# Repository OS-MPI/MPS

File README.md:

# The Magnetic Particle Spectroscopy (MPS) device
# [Link to the wiki](https://github.com/OS-MPI/MPS/wiki)
# [Link to the Main OS-MPI Page](https://os-mpi.github.io/)

## Motivation and Introduction

The system we are calling the MPS device is a low cost, and fairly simple to manufacture project which more generally speaking is a platform designed around understanding magnetic characteristics of superparamagentic iron oxide nanoparticles (SPIONs). The motivation was to condense the numerous existing systems into a singlular platform capable of providing insights into the nanoparticles irrespective of the specific goal of the lab. With that in mind, calling our platform an "MPS" system is rather imprecise; while one mode is traditional "spectroscopy" the device is designed to be flexible and able to perform relaxometry measurements as well as magnetometry, yet in order to give the project an easy-to-find, descriptive name, we settled on the "magnetic particle spectroscopy" system. 

## State of the project

In the current state (of March 2024) we have the system working in all [primary operational modes](https://github.com/OS-MPI/MPS/wiki/Modes-of-operation). It is capable of sensitively detecting SPIONs to the ng Fe level, quantifying the magnetization spectra, tracing the hysteresis loops, etc. 

The primary focus now is improving the documentation.

## System overview

Broadly speaking, there are four principle hardware components, the three coils (drive, receive, and bias) and the sample positioner. The drive coils produce magnetic fields (typ. 10 mT) which cause the SPIONs within the bore to go into and out of saturation at 23.8 kHz. This changing magnetism induces a voltage in the receive coils. The bias coils allow for the quasistatic operating point of the SPIONs to be modulated by generating low frequency (~10 Hz) fields up to about 50 mT.

### Drive/Transmit system
The drive system consists of the drive coils as well as the amplifier and filter. 

The drive coil is seen in the photograph above (the larger coil with four sub-sections). All of the four winding sections are in the same handedness. See the Wiki for further details. 

In this photograph, we utilize an in-house made Litz wire (18 strands of 28 AWG magnet wire), although other Litz wires may work similarly well. Previously a commercial Litz wire with 115 strands of 36AWG was used, but because of the plastic sleeve over the wires, they could not be easily stabilized with epoxy. 

The drive filter serves to purify and the waveform produced by the amplifier. Most amplifiers produce about 0.1% (or worse) total harmonic distortion, so without this filter those amplifier-generated distortions will dominate the noise floor. That being said, its among the most challenging components to manufacture, so its worth discussing which components are essential, and which are more or less optional. Refering to the schematic below, the two most important sections are the tuning/matching capacitors (C1 and C2), and the transformer (LPri and LSec). The tuning capacitors form a resonant circuit with Ldrive (the drive coil's equivalent load). This can be seen if you notice the loop formed by C1 C2 and LDrive is resonant. The choice of values for C1 and C2 is to make the equivalent impedance 8 ohms or so. The transformer should be a ferrite such as N87 and be designed such that the core flux is well below saturation (~20x lower, so 20ish mT). The purpose is to mitigate common-mode noise and provide isolation/break any ground loops. The other filter components can be "dropped in" later without disturbing the overall circuit. But these additional filtering components are both the most challenging to build, and less necessary. 

Many different drive amplifiers can be used. We have used both linear and switch-mode amplifiers with success. For a basic system, the AIYIMA A07 can be used, or other amplifiers based on the TPA3255 will likely be good choices. For example Nobsound G2 pro is also likely good and is pre-configured to be in PBTL mode. That IC from Texas Instruments has excellent performance given the cost and high switching frequency. The AE Techron 7224 is considerably more expensive, but produces a much higher fidelity waveform and has far more power available.

### Receive system

The receive system consists of the gradiometer receive coils, the filter, matching transformer, and preamplifier. The receive coil is a simple gradiometer to mitigate the net voltage induced from the changing magnetic drive fields (60-80 dBc attenuation of the voltage is a reasonable target). The filter reduces the amplitude of the signal at the drive frequency, but doesnt fully remove it. The matching transformer steps up the voltage produced by the receive coil (post filter) to improve the noise performance of the system. The transformer also provides isolation and common-mode supression, which help signal fidelity. The preamplifier amplifies the signal to a level more usable by the data acquisition hardware. In our case, we digitize the signals with a National Instruments NI PXIe 6363 and 6361. 

### Bias system

The bias system applies a low frequency (~10Hz), high amplitude waveform to probe the magnetization response at different quasistatic operating points. "Quasistatic" is emphasized here just because we utilize the assumption that this frequency is so low relaxation effects are negligible.

The system was initially designed to allow for even very small SPIONs (e.g. 5nm) to be probed out toward saturation, so many turns were added and cooling spaces were added to allow air to pass between the windings. With this design, passive convection is sufficient for normal operation at 50 mT peak. For up to 100 mT peak, lower duty cycles, or forced air should be used. 

This coil can be neglected if only hysteresis loop tracing or spectroscopy modes will be used. In that case, the diameter of the shielding tube should be increased to about 50-60 mm diameter. 

### Sample positioner

An automatic sample positioner is used to allow for consistent placement of the SPIONs as well as having the sample move in and out repeatedly to allow for multiple baselines to acquired. 

### Software

The software is written with LabVIEW 2021. Labview is not backwards compatible, so it must be operated with version 2021 or newer. 

With any issues regarding the project or missing files/documentation, [please reach out to the authors of this project here](https://github.com/OS-MPI/MPS/wiki/Contact-Us).

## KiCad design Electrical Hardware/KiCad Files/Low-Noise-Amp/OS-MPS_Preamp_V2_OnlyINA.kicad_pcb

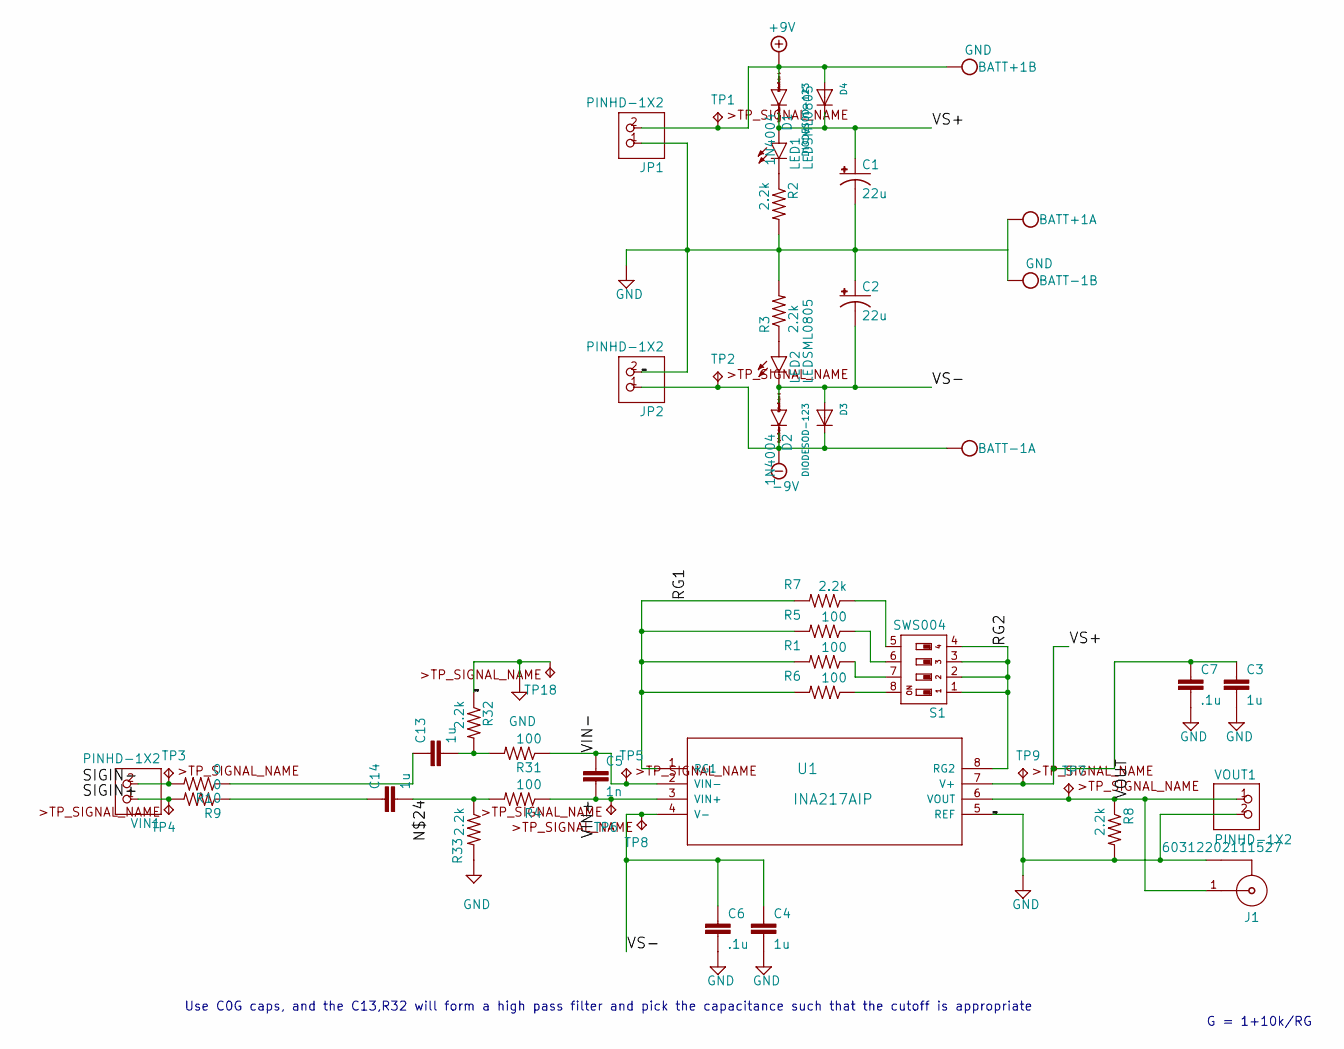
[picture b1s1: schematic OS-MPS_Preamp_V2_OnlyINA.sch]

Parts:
BATT+1: GND; W237-102
BATT-1: GND; W237-102
C1, C2: 22u; TT2D6
C3, C4, C13, C14: 1u; C1206
C5: 1n; C1206
C6, C7: .1u; C1206
D1, D2: 1N4004; DO41-10
D3, D4: DIODESOD-123; SOD-123
J1: 60312202111527
JP1, JP2: PINHD-1X2; 1X02
LED1, LED2: LEDSML0805; SML0805
R1, R4, R5, R6, R31: 100; R0805
R2, R3, R7, R8, R32, R33: 2.2k; R0805
R9, R10: 0; R0805
S1: SWS004; SMS-004
TP1, TP2: TPB2,54; B2,54
TP3, TP4, TP5, TP6, TP7, TP8, TP9, TP18: TPTP20SQ; TP20SQ
U1: INA217AIP; P8
VIN1: PINHD-1X2; 1X02
VOUT1: PINHD-1X2; 1X02

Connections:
+9V: BATT+1.2, D1.A, D4.A, JP1.2, TP1.TP
-9V: BATT-1.1, D2.C, D3.C, JP2.1, TP2.TP
/N$24: C14.2, R4.2, R33.1
/RG1: R1.2, R5.2, R6.2, R7.2, U1.1 (RG1)
/RG2: S1.1, S1.2, S1.3, S1.4, U1.8 (RG2)
/SIGIN+: R9.2, TP4.TP, VIN1.1
/SIGIN-: R10.2, TP3.TP, VIN1.2
/VIN+: C5.2, R4.1, TP6.TP, U1.3 (VIN+)
/VIN-: C5.1, R31.1, TP5.TP, U1.2 (VIN-)
/VOUT: J1.1, R8.1, TP7.TP, U1.6 (VOUT), VOUT1.1
/VS+: C1.+, C3.1, C7.1, D1.C, D4.C, LED1.A, TP9.TP, U1.7 (V+)
/VS-: C2.-, C4.1, C6.1, D2.A, D3.A, LED2.C, TP8.TP, U1.4 (V-)
GND: BATT+1.1, BATT-1.2, C1.-, C2.+, C3.2, C4.2, C6.2, C7.2, J1.2, J1.3 (2), J1.4 (2), J1.5 (2), JP1.1, JP2.2, R2.2, R3.2, R8.2, R32.1, R33.2, TP18.TP, U1.5 (REF), VOUT1.2
unnamed: C13.1, R10.1
unnamed: C13.2, R31.2, R32.2
unnamed: C14.1, R9.1
unnamed: LED1.C, R2.1
unnamed: LED2.A, R3.1
unnamed: R1.1, S1.7
unnamed: R5.1, S1.6
unnamed: R6.1, S1.8
unnamed: R7.1, S1.5

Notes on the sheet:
Use C0G caps, and the C13,R32 will form a high pass filter and pick the capacitance such that the cutoff is appropriate
G = 1+10k/RG

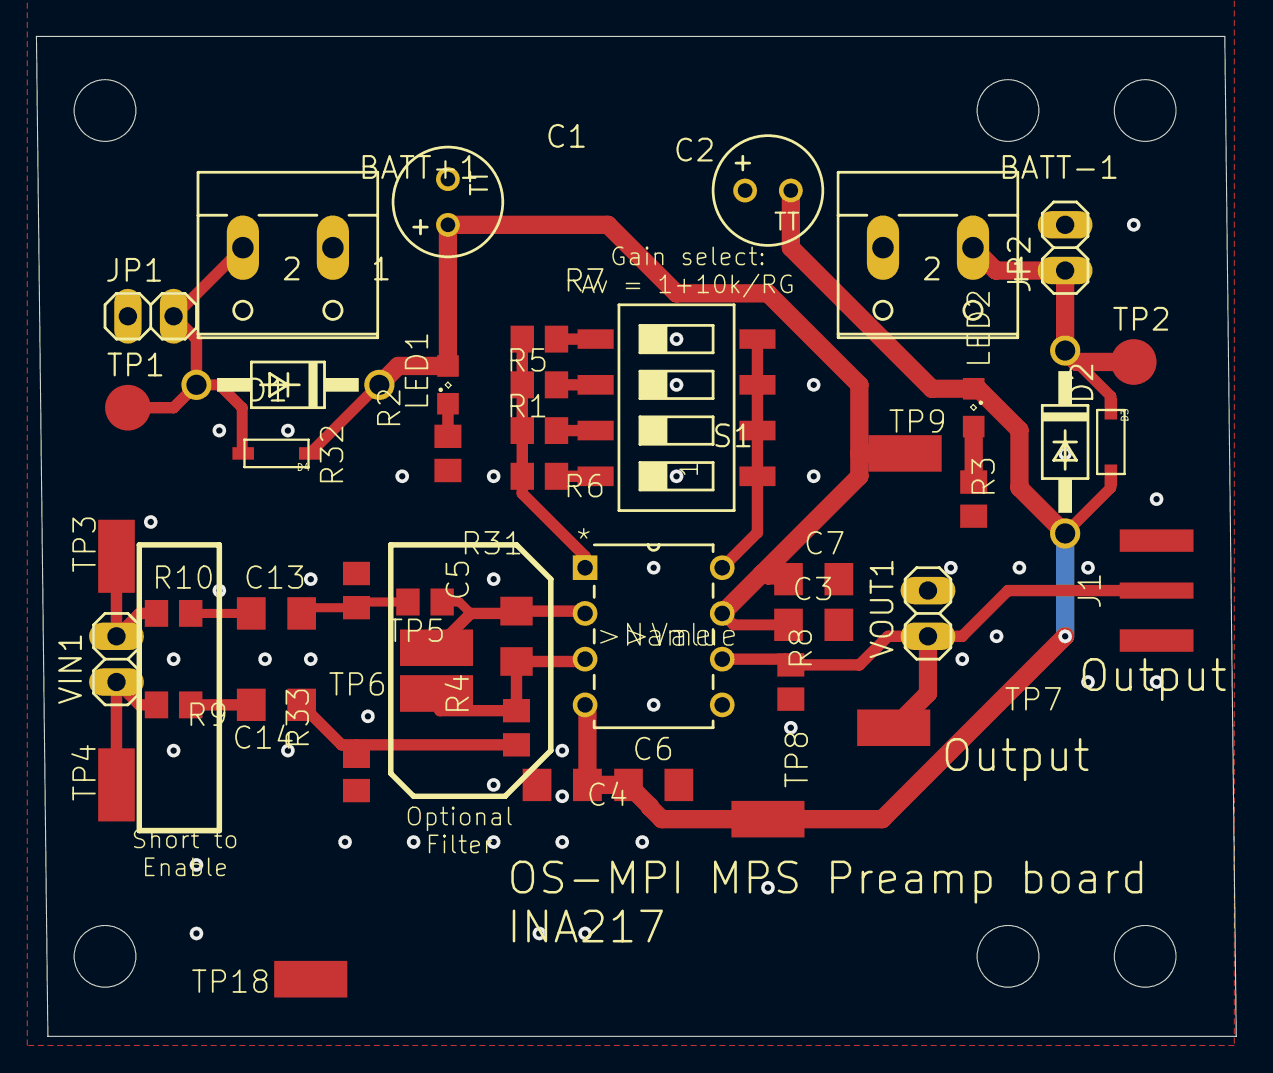
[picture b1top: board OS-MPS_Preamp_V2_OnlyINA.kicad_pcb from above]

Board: 2 copper layers, 66.7 x 55.6 mm, 53 parts (0 on the bottom side), 22 nets.

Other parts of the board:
@HOLE0, @HOLE1, @HOLE2, @HOLE3, @HOLE4, @HOLE5: (no value)

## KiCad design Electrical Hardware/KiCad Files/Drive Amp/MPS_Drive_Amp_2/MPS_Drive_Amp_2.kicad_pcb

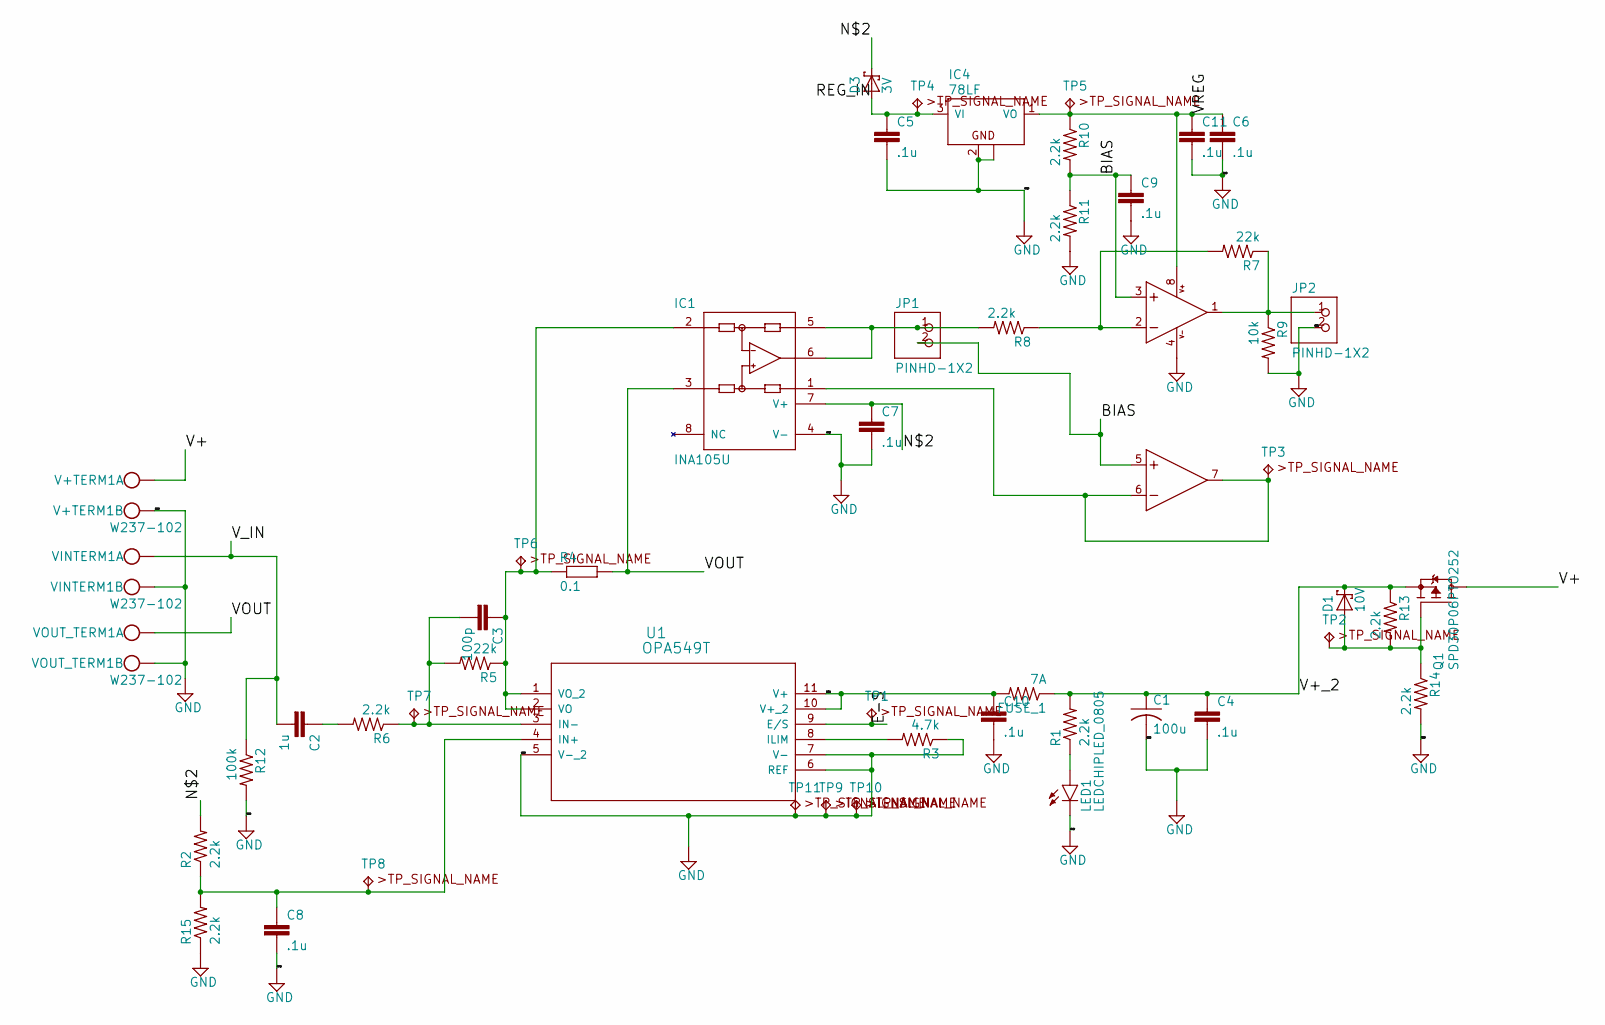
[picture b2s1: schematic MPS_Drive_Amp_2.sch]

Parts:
C1: 100u; C050-025X075
C2: 1u; C1206
C3: 100p; C1206
C4, C5, C6, C7, C8, C9, C10, C11: .1u; C1206
D1: 10V; DO35-7
D3: 3V; DO35-7
FUSE_1: 7A; R1206
IC1: INA105U; SO08
IC2: LM358MX; SO08
IC4: 78LF; SOT89
JP1, JP2: PINHD-1X2; 1X02
LED1: LEDCHIPLED_0805; CHIPLED_0805
Q1: SPD30P06PTO252; TO252
R1, R2, R6, R8, R10, R11, R13, R14, R15: 2.2k; R1206
R3: 4.7k; R1206
R4: 0.1; VTA52
R5, R7: 22k; R1206
R9: 10k; R1206
R12: 100k; R1206
TP1, TP2, TP3, TP4, TP5, TP6, TP7, TP8, TP9, TP10, TP11: TPTP20SQ; TP20SQ
U1: OPA549T; KV11
V+TERM1: W237-102
VINTERM1: W237-102
VOUT_TERM1: W237-102

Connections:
/BIAS: C9.1, IC2.3 (+IN), IC2.5 (+IN), JP1.2, R10.2, R11.1
/E-S: TP1.TP, U1.9 (E/S)
/N$2: C7.1, C10.1, D3.C, FUSE_1.2, IC1.7 (V+), R2.2, U1.10 (V+_2), U1.11 (V+)
/REG_IN: C5.1, D3.A, IC4.3 (VI), TP4.TP
/V+: Q1.3 (D), V+TERM1.1
/V+_2: C1.1, C4.1, D1.C, FUSE_1.1, Q1.2 (S), R1.2, R13.1
/VOUT: IC1.3 (+IN), R4.2, VOUT_TERM1.1
/VREG: C6.1, C11.1, IC2.8 (V+), IC4.1 (VO), R10.1, TP5.TP
/V_IN: C2.2, R12.1, VINTERM1.1
GND: C1.2, C4.2, C5.2, C6.2, C7.2, C8.2, C9.2, C10.2, C11.2, IC1.4 (V-), IC2.4 (V-), IC4.2 (GND), IC4.2@1 (GND@1), JP2.2, LED1.C, R3.1, R9.2, R11.2, R12.2, R14.2, R15.1, TP9.TP, TP10.TP, TP11.TP, U1.5 (V-_2), U1.6 (REF), U1.7 (V-), V+TERM1.2, VINTERM1.2, VOUT_TERM1.2
unnamed: C2.1, R6.2
unnamed: C3.1, IC1.2 (-IN), R4.1, R5.1, TP6.TP, U1.1 (VO_2), U1.2 (VO)
unnamed: C3.2, R5.2, R6.1, TP7.TP, U1.3 (IN-)
unnamed: C8.1, R2.1, R15.2, TP8.TP, U1.4 (IN+)
unnamed: D1.A, Q1.1 (G), R13.2, R14.1, TP2.TP
unnamed: IC1.1 (REF), IC2.6 (-IN), IC2.7 (OUT), TP3.TP
unnamed: IC1.5 (SENSE), IC1.6 (OUT), JP1.1, R8.2
unnamed: IC2.1 (OUT), JP2.1, R7.1, R9.1
unnamed: IC2.2 (-IN), R7.2, R8.1
unnamed: LED1.A, R1.1
unnamed: R3.2, U1.8 (ILIM)

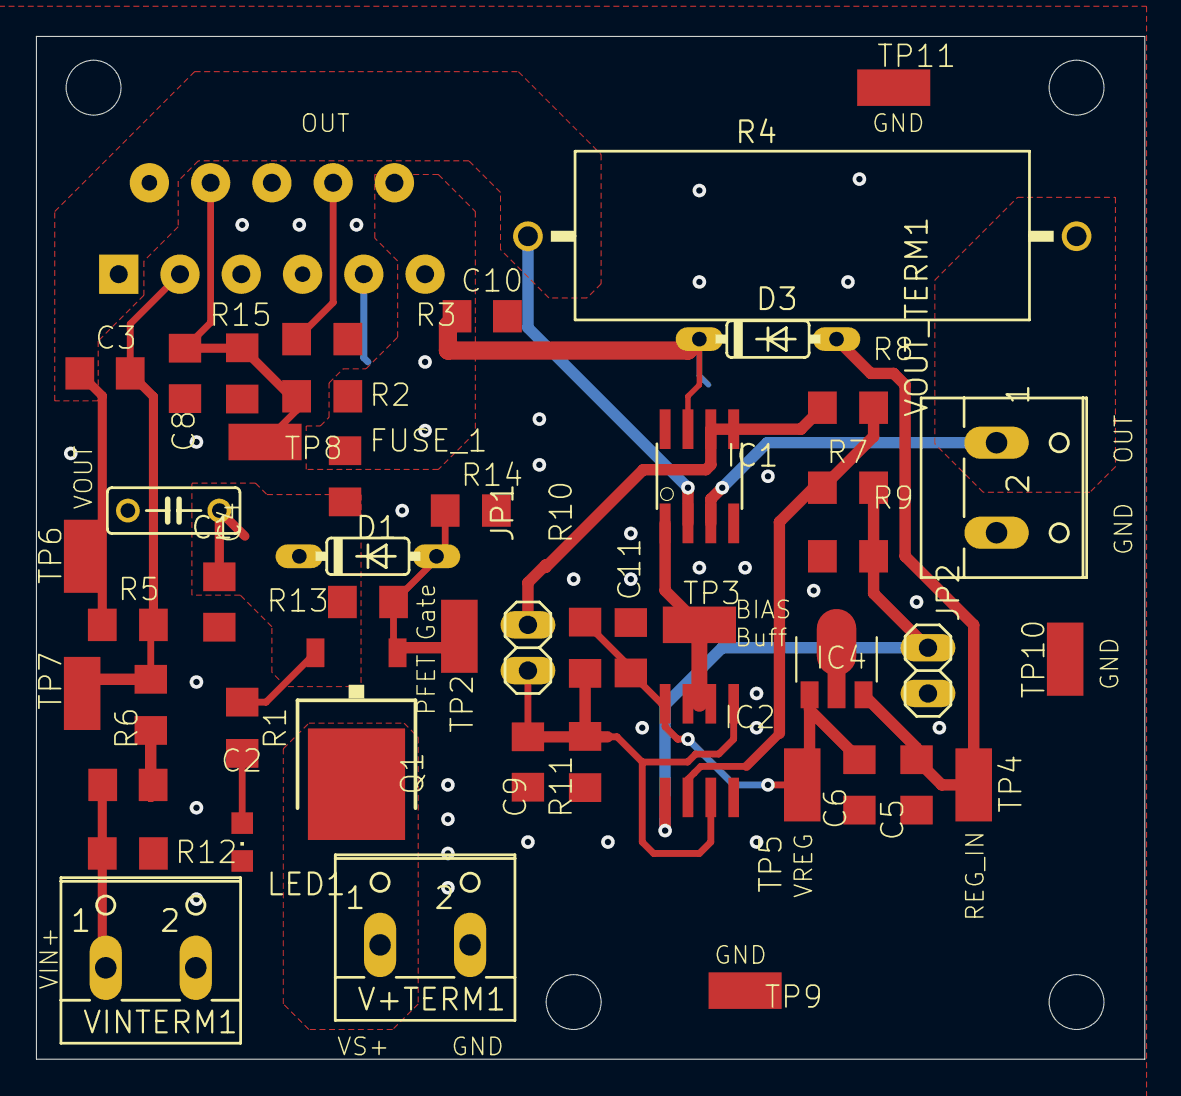
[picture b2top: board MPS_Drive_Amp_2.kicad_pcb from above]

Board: 2 copper layers, 61.6 x 56.8 mm, 55 parts (0 on the bottom side), 21 nets.

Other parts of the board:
@HOLE0, @HOLE1, @HOLE2, @HOLE3: (no value)

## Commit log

2019-12-01 Updatet_Part sheet
2019-12-02 Add Design Scripts
2020-02-17 Initial Inventor Part Push
2020-02-17 First MATLAB Script Push
2020-02-17 MATLAB Some Comments
    More commenting and cleaning code to come!
2020-02-17 Status Update README
2020-02-24 Updates and comments
2020-04-13 Update MATLAB Scripts
2020-07-22 Update Functions
2020-07-28 Update Scripts
2020-08-03 Update Many Scripts_ AddFullAnalysis
2020-08-03 Electrical Documentation
    Add LT Spice and PCB files
2020-08-04 Update TF Figure and ReadMe
2020-08-06 Update MATLAB
2020-08-14 Update Acquisition Scripts
2020-08-14 Add Example Data
2020-08-14 Update Composite Fig Function
2020-09-07 Update Scripts and BOM
2020-09-14 Update Inventor Files
2020-09-15 Update Inventor
2021-05-13 Add PCB BOM
    The BOM has been updated and PCB assembly files were added
2021-05-19 Version 2 initial update
    Initial update of files
2021-05-19 Update Inventor Part files
2021-05-20 Add Render and STEP file
2021-05-20 Update BOM for PreAmp
2021-06-06 Update Preamp Files
    Making them more compatible with fab.
2021-06-06 Update BOM/PnP
2021-07-07 Update sample holder+AA filter
2021-07-08 Update CAD
2021-07-08 Add STEP assembly
2021-07-08 PCB Pictures
2021-07-12 Update Bias optimization
2021-11-02 Add Comment
2021-11-02 Add KiCAD imported files
2022-04-08 Bulb Holders
2022-10-12 Filter Demo files
2022-10-12 New Drive coil FEMM
2022-11-01 Add results, update readme
2022-11-04 Reorganize files, archive old
2023-01-07 Inventor parts and labview
2023-01-07 Labview and Kicad
2023-01-16 Revert "Labview and Kicad"
    This reverts commit 51e892e73b62c1425be5d503678960fc262d96d0.
2023-01-16 Revert "Merge branch 'master' of https://github.com/OS-MPI/MPS"
    This reverts commit 0830b3b2eac63f10c73bfe72329d2da439e7747c, reversing
    changes made to c0ffb2e8f59d7c4befeacfec3356fb3a495e5a89.
2023-01-16 Demo Cross Section
2023-05-31 Inventor files
2023-07-01 Initialize Labview
2024-03-21 Move parts to archive
2024-03-21 Updated inventor files
2024-03-22 Update inventor assm
